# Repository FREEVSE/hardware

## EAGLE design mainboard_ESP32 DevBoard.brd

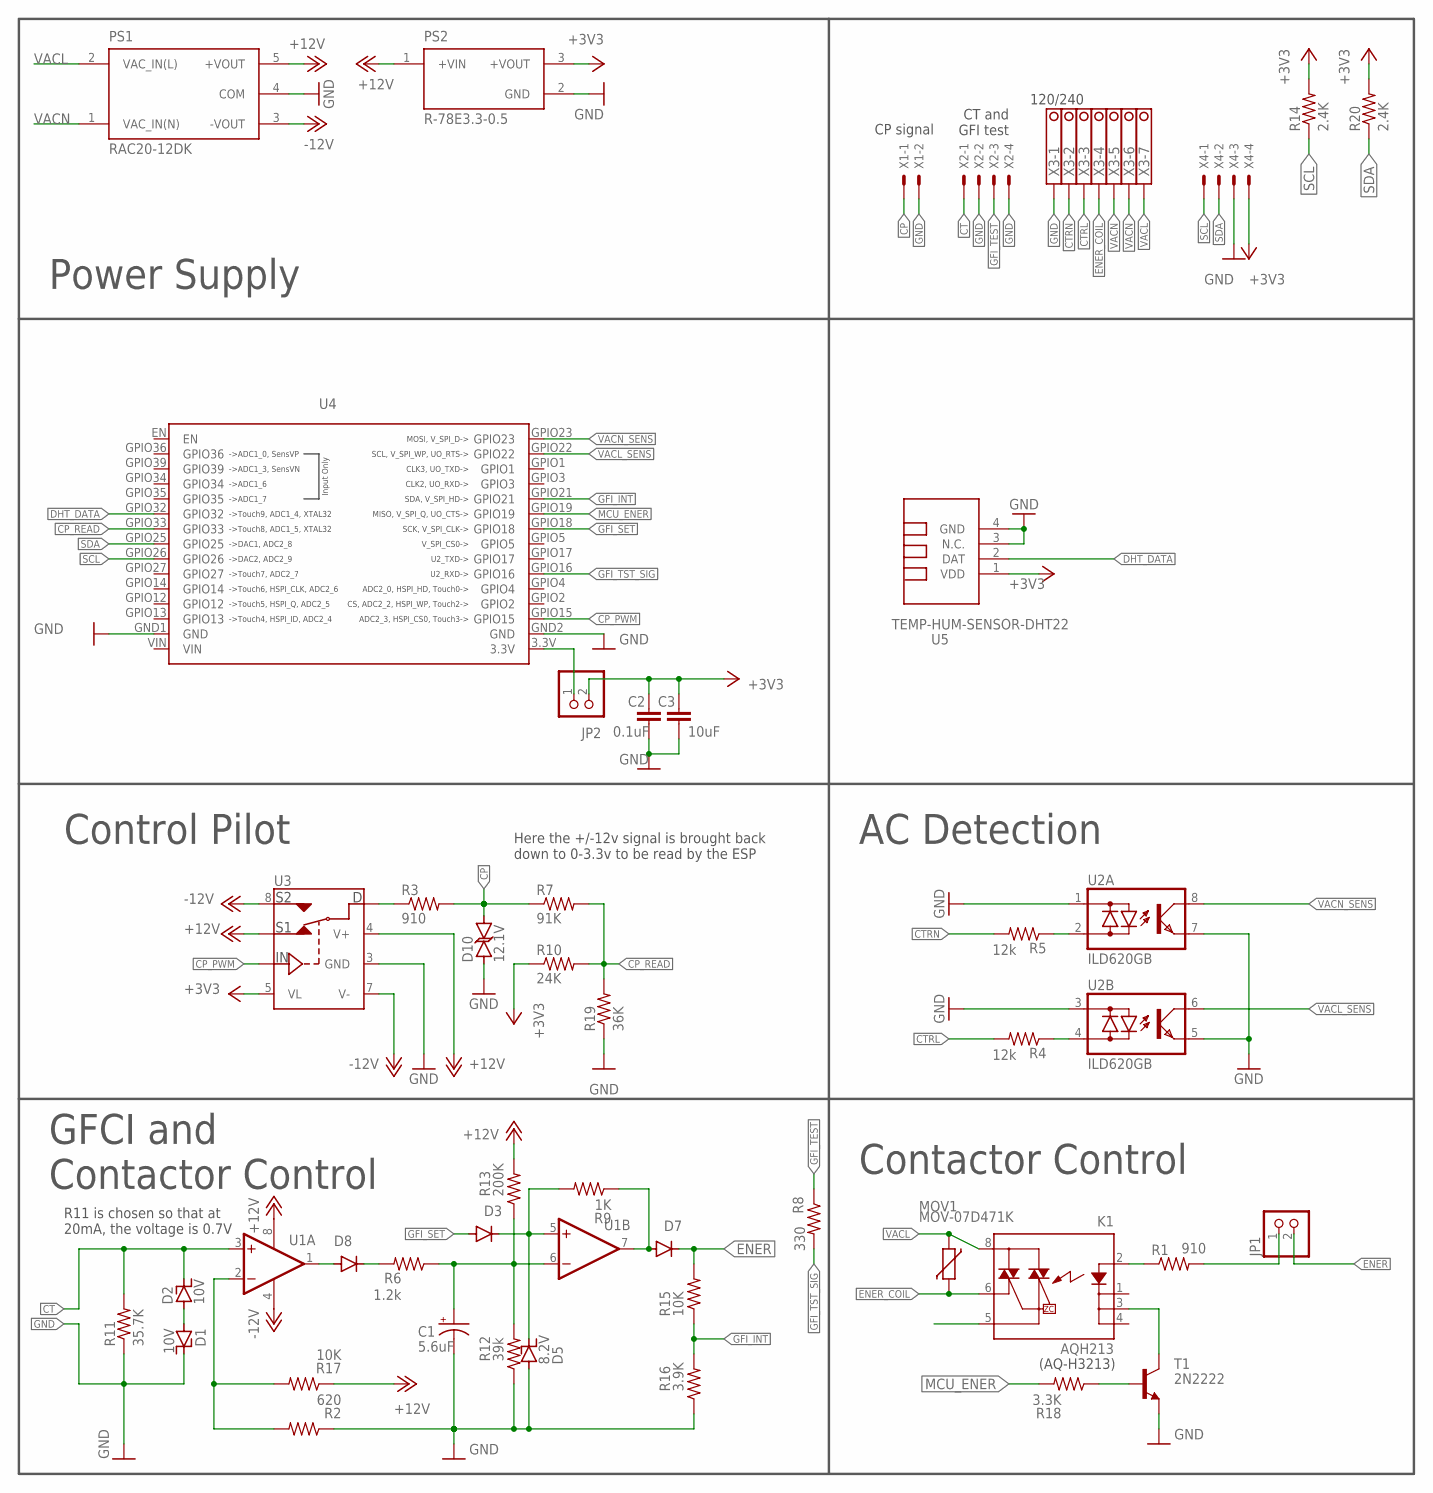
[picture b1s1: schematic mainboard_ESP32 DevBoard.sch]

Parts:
C1: 5.6uF; E2-5
C2: 0.1uF; C025-025X050
C3: 10uF; C025-050X050
D1, D2: 10V; DO35-7
D3, D7, D8: 1N4148DO35-7; DO35-7
D5: 8.2V; DO35-7
D10: 12.1V; DO15
JP1: PINHD-1X2; 1X02
JP2: PINHD-1X2/90; 1X02/90
K1: AQH213; DIL07
MOV1: MOV-07D471K; DISC-7
PS1: RAC20-12DK; CONV_RAC20-12DK
PS2: R-78E3.3-0.5; CONV_R-78E3.3-0.5
R1, R3: 910; 0204/7-L
R2: 620; 0204/7-L
R4, R5: 12k; 0204/7-L
R6: 1.2k; 0204/7-L
R7: 91K; 0204/7-L
R8: 330; 0204/7-L
R9: 1K; 0204/7-L
R10: 24K; 0204/7-L
R11: 35.7K; 0204/7-L
R12: 39k; 0204/7-L
R13: 200K; 0204/7-L
R14, R20: 2.4K; 0204/7-L
R15, R17: 10K; 0204/7-L
R16: 3.9K; 0204/7-L
R18: 3.3K; 0204/7-L
R19: 36K; 0204/7-L
T1: 2N2222; TO92-EBC
U1: LM833N; DIL08-LONG
U2: ILD620GB; DIL8
U3: DG419DJ-L; DIL08-LONG
U4: ESP32-DOIT-V1
U5: TEMP-HUM-SENSOR-DHT22
X1: JST-XH-02-PIN-LONG-PAD; JST-XH-02-PACKAGE-LONG-PAD
X2, X4: JST-XH-04-PIN-LONG-PAD; JST-XH-04-PACKAGE-LONG-PAD
X3: 1751293

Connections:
+3V3: C2.1, C3.1, JP2.2, PS2.3 (+VOUT), R10.1, R14.2, R20.2, U3.5 (VL), U5.1 (VDD), X4.4
+12V: PS1.5 (+VOUT), PS2.1 (+VIN), R13.2, R17.1, U1.8 (V+), U3.2 (S1), U3.4 (V+)
-12V: PS1.3 (-VOUT), U1.4 (V-), U3.7 (V-), U3.8 (S2)
CP: D10.C, R3.2, R7.1, X1.1
CP_PWM: U3.6 (IN), U4.GPIO15
CP_READ: R7.2, R10.2, R19.2, U4.GPIO33
CT: D2.C, R11.2, U1.3 (+IN), X2.1
CTRL: R4.2, X3.3
CTRN: R5.2, X3.2
DHT_DATA: U4.GPIO32, U5.2 (DAT)
ENER: D7.C, JP1.2, R15.2
ENER_COIL: K1.6 (DS3), MOV1.P$2 (2), X3.4
GFI_INT: R15.1, R16.2, U4.GPIO21
GFI_SET: D3.A, U4.GPIO18
GFI_TEST: R8.1, X2.3
GFI_TST_SIG: R8.2, U4.GPIO16
GND: C1.-, C2.2, C3.2, D1.C, D5.A, D10.A, PS1.4 (COM), PS2.2 (GND), R2.1, R11.1, R12.1, R16.1, R19.1, T1.E, U2.1 (AC1), U2.3 (AC1), U2.5 (E), U2.7 (E), U3.3 (GND), U4.GND1 (GND), U4.GND2 (GND), U5.3 (N.C.), U5.4 (GND), X1.2, X2.2, X2.4, X3.1, X4.3
MCU_ENER: R18.2, U4.GPIO19
unnamed: K1.2 (A), R1.1
unnamed: R2.2, R17.2, U1.2 (-IN)
unnamed: JP1.1, R1.2
unnamed: D7.A, R9.1, U1.7 (OUT)
unnamed: D1.A, D2.A
unnamed: D8.C, R6.2
unnamed: R3.1, U3.1 (D)
unnamed: C1.+, R6.1, R12.2, R13.1, U1.6 (-IN)
unnamed: JP2.1, U4.3.3V
unnamed: R18.1, T1.B
unnamed: D3.C, D5.C, R9.2, U1.5 (+IN)
unnamed: K1.3 (K1), T1.C
unnamed: D8.A, U1.1 (OUT)
unnamed: R5.1, U2.2 (AC2)
unnamed: R4.1, U2.4 (AC2)
SCL: R14.1, U4.GPIO26, X4.1
SDA: R20.1, U4.GPIO25, X4.2
VACL: K1.8 (DS1), MOV1.P$1 (1), PS1.2 (VAC_IN(L)), X3.7
VACL_SENS: U2.6 (C), U4.GPIO22
VACN: PS1.1 (VAC_IN(N)), X3.5, X3.6
VACN_SENS: U2.8 (C), U4.GPIO23
VIN: U4.VIN

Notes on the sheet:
Here the +/-12v signal is brought back down to 0-3.3v to be read by the ESP
Control Pilot
(AQ-H3213)
GFCI and Contactor Control
CP signal
CT and GFI test
120/240
Power Supply
R11 is chosen so that at 20mA, the voltage is 0.7V
AC Detection
Contactor Control

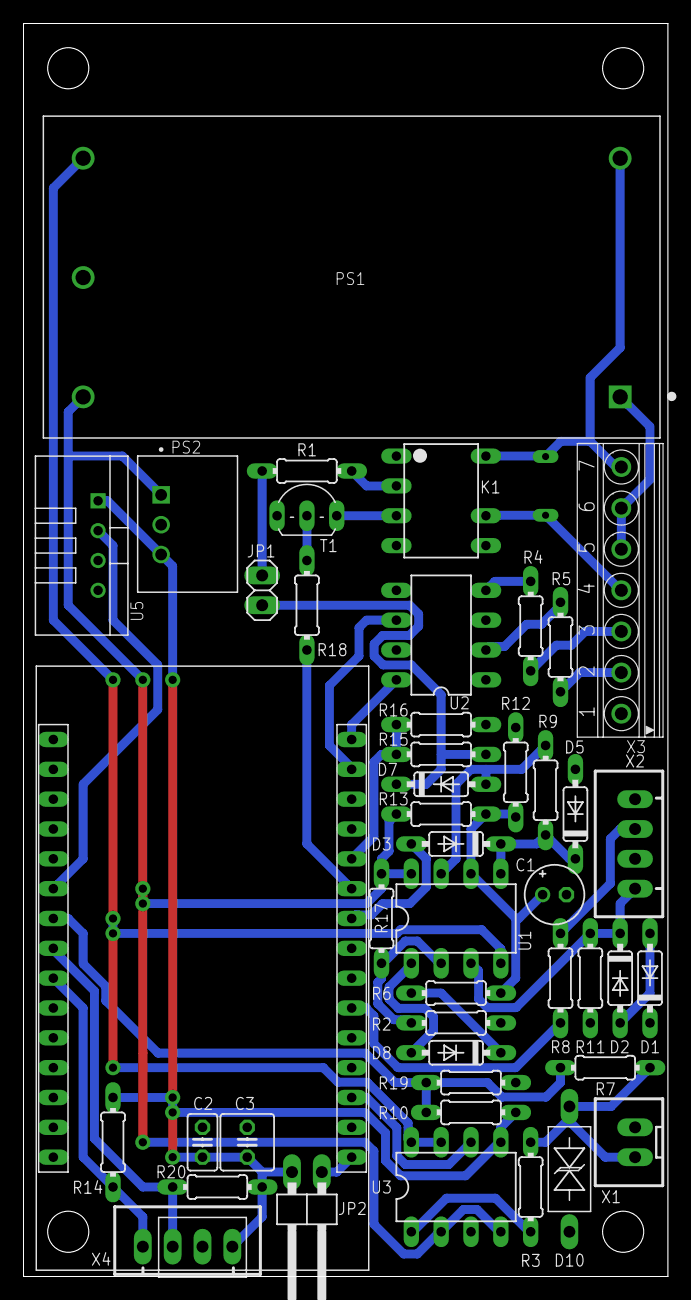
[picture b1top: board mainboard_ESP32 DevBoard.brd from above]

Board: 2 copper layers, 54.9 x 106.7 mm, 46 parts (0 on the bottom side), 39 nets.

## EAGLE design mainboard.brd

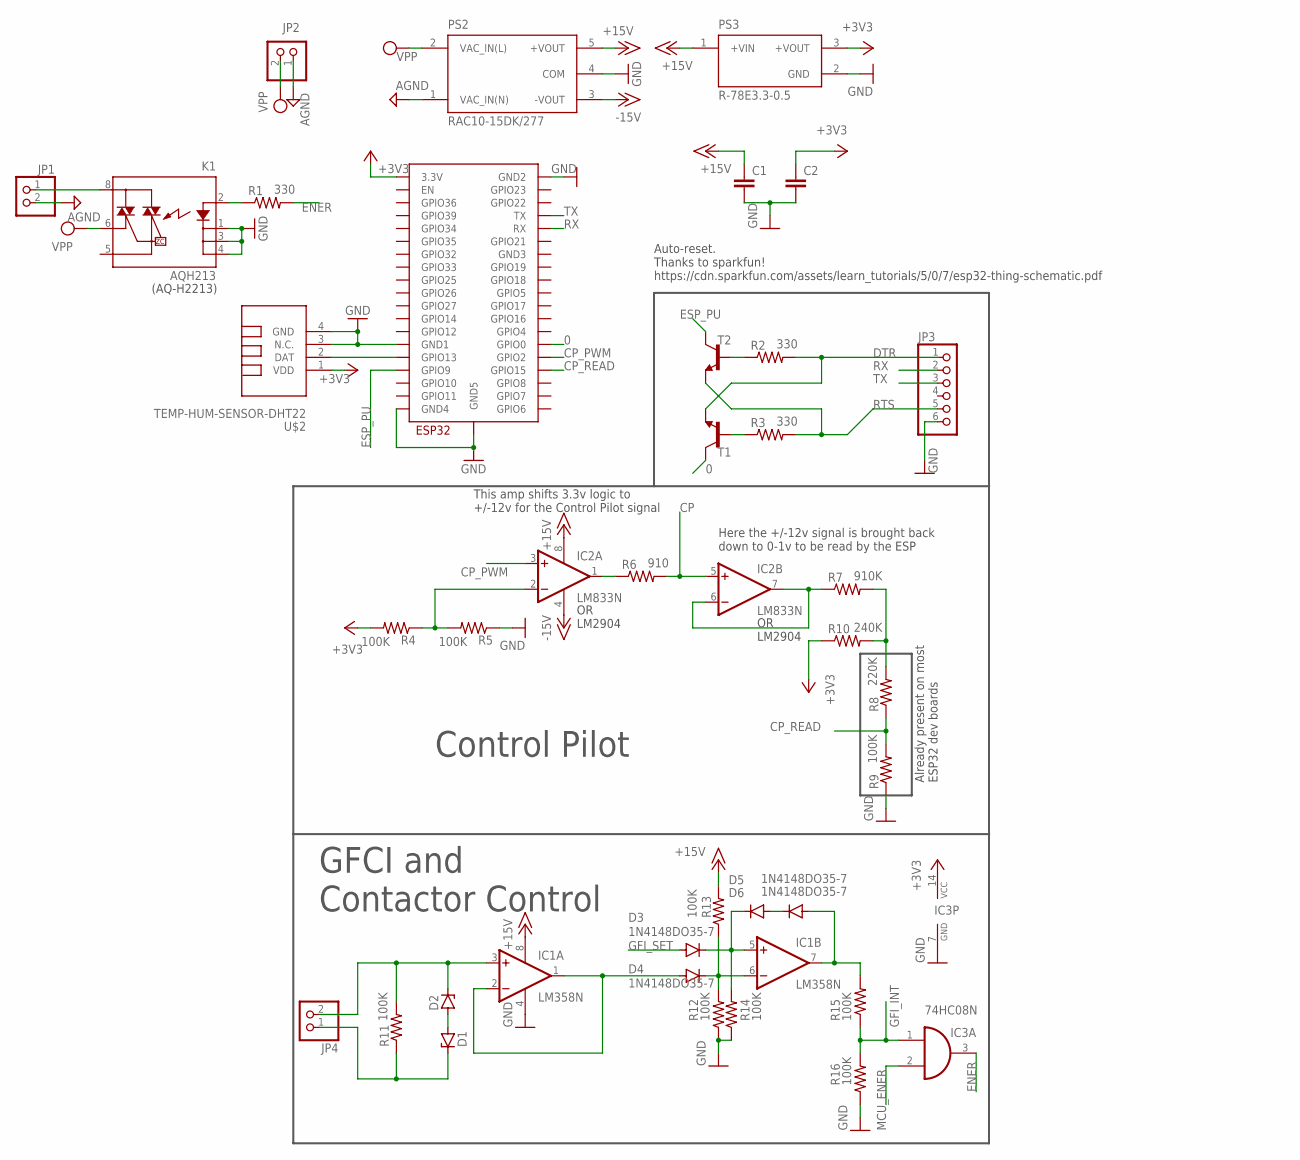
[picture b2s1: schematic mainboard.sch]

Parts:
C1, C2: C-EU025-025X050; C025-025X050
D1, D2: ZENER-DIODEDO34-7; DO34Z7
D3, D4, D5, D6: 1N4148DO35-7; DO35-7
IC1: LM358N; DIL08
IC2: LM833N; DIL08
IC3: 74HC08N; DIL14
JP1, JP2, JP4: PINHD-1X2; 1X02
JP3: PINHD-1X6; 1X06
K1: AQH213; DIL07
PS2: RAC10-15DK/277; CONV_RAC10-15DK/277
PS3: R-78E3.3-0.5; CONV_R-78E3.3-0.5
R1, R2, R3: 330; 0204/7
R4, R5, R9, R11, R12, R13, R14, R15, R16: 100K; 0204/7
R6: 910; 0204/7
R7: 910K; 0204/7
R8: 220K; 0204/7
R10: 240K; 0204/7
T1, T2: MMBT3904LT1-NPN-SOT23-BEC; SOT23-BEC
U$1: ESP32-WROOM
U$2: TEMP-HUM-SENSOR-DHT22

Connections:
0: T1.C, U$1.IO0 (GPIO0)
+3V3: C2.1, IC3.14 (VCC), PS3.3 (+VOUT), R4.2, R10.1, U$1.3V3 (3.3V), U$2.1 (VDD)
+15V: C1.1, IC1.8 (V+), IC2.8 (V+), PS2.5 (+VOUT), PS3.1 (+VIN), R13.2
-15V: IC2.4 (V-), PS2.3 (-VOUT)
AGND: JP1.2, JP2.1, PS2.1 (VAC_IN(N))
CP: IC2.5 (+IN), R6.2
CP_PWM: IC2.3 (+IN), U$1.IO2 (GPIO2)
CP_READ: R8.1, R9.2, U$1.IO15 (GPIO15)
DTR: JP3.1, R2.2, T1.E
ENER: IC3.3 (O), R1.2
ESP_PU: T2.C, U$1.SD2 (GPIO9)
GFI_INT: IC3.1 (I0), R15.1, R16.2
GFI_SET: D3.A
GND: C1.2, C2.2, IC1.4 (V-), IC3.7 (GND), JP3.6, K1.1 (K), K1.3 (K1), K1.4 (K2), PS2.4 (COM), PS3.2 (GND), R5.1, R9.1, R12.1, R14.1, R16.1, U$1.GND1, U$1.GND2, U$1.GND4, U$1.GND5, U$2.3 (N.C.), U$2.4 (GND)
MCU_ENER: IC3.2 (I1)
unnamed: K1.2 (A), R1.1
unnamed: JP1.1, K1.8 (DS1)
unnamed: U$1.IO13 (GPIO13), U$2.2 (DAT)
unnamed: D1.A, D2.A
unnamed: D2.C, IC1.3 (+IN), JP4.2, R11.2
unnamed: R2.1, T2.B
unnamed: R3.1, T1.B
unnamed: D4.A, IC1.1 (OUT), IC1.2 (-IN)
unnamed: D1.C, JP4.1, R11.1
unnamed: D6.A, IC1.7 (OUT), R15.2
unnamed: D5.A, D6.C
unnamed: D3.C, D5.C, IC1.5 (+IN), R14.2
unnamed: D4.C, IC1.6 (-IN), R12.2, R13.1
unnamed: IC2.2 (-IN), R4.1, R5.2
unnamed: IC2.1 (OUT), R6.1
unnamed: IC2.6 (-IN), IC2.7 (OUT), R7.1
unnamed: R7.2, R8.2, R10.2
RTS: JP3.5, R3.2, T2.E
RX: JP3.2, U$1.RX
TX: JP3.3, U$1.TX
VPP: JP2.2, K1.6 (DS3), PS2.2 (VAC_IN(L))

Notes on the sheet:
Already present on most ESP32 dev boards
This amp shifts 3.3v logic to +/-12v for the Control Pilot signal
Here the +/-12v signal is brought back down to 0-1v to be read by the ESP
OR LM2904
Auto-reset. Thanks to sparkfun! https://cdn.sparkfun.com/assets/learn_tutorials/5/0/7/esp32-thing-schematic.pdf
Control Pilot
(AQ-H2213)
GFCI and Contactor Control

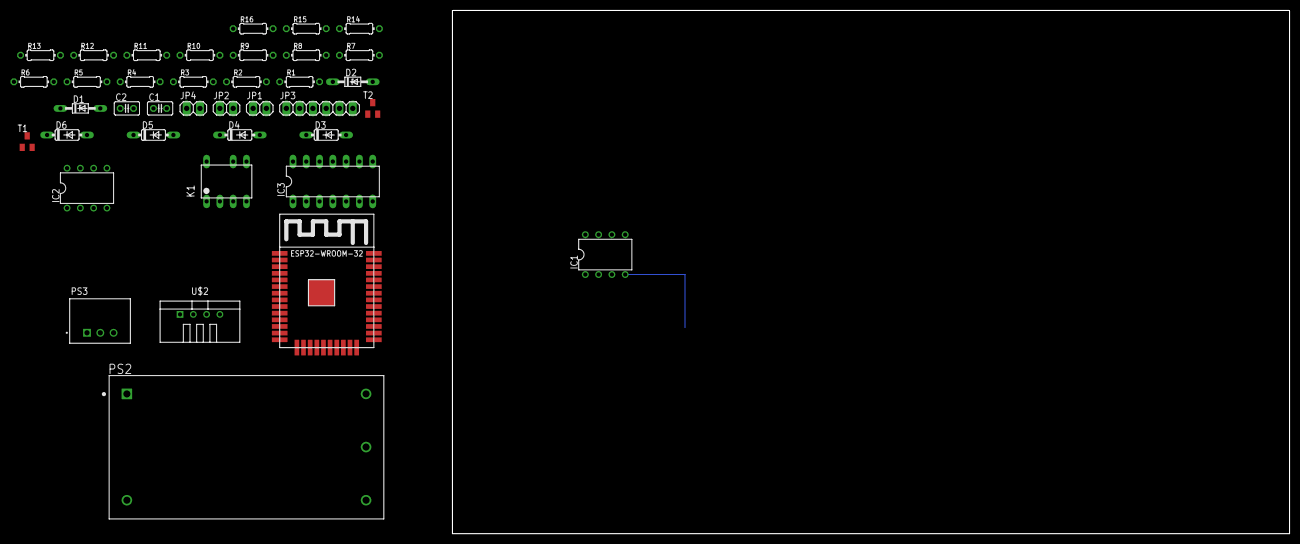
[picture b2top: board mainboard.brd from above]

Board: 2 copper layers, 160.0 x 100.0 mm, 38 parts (0 on the bottom side), 34 nets.

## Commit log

2019-12-28 Completed routing first try of board. Some pin changes to fit the board better. Added puldown and jumper to prevent accidental coil energize.
2019-12-29 Tweaked resistor on GFI circuit to allow 3.3v logic to set the latch
2019-12-29 Added header to disconnect 3.3v output from esp to 3.3 rail. Added LED to indicate when contactor is energized. Added I2C connector. Added mounting holes.
2019-12-31 Made all traces as big as possible. Pads also. Added some layers for CAM outputs. Added cam job file
2020-01-10 Updated ignore file. Made some adjustments after making the first board.
2020-01-13 Made board single-sided friendly (P2P wiring needed). Tweaked some more resistor values. Added missing resistor to CP read level shifter
2020-01-13 Corrected some via sizes
2020-01-16 Switched to +-12v, tweaked some R values to fit new psu. Also swapped CP opamp for an r2r one
2020-02-11 Added DG419 in place of op amp.
2020-04-30 Added optos for sensing L and N (l1/l2)
2020-05-11 Moved resistor on line sense for a tight, but good fit. cam outputs used for board 2
2020-05-13 Added missing mains class
2020-05-17 Added header for ac detection after contactor. Cleaned up schematic.
2020-05-19 Swapped ac headers for one big one and added dedicated earth terminal
2020-06-25 Adjusted labels for PCB manufacture
2020-07-01 Cleaned labels
2020-07-11 Reworked GFCI to account for noise on the line. Swapped out AND gate for 2 mosfets. Removed mostly useless caps from PSU outputs, caps should be closer to devices
2020-07-17 Re-worked GFCI to be tolerant of transient spikes. Removed some components because of it
2020-07-26 Completed new GFCI circuit
2020-07-31 Corrected some component values that were wrong during assembly
2020-07-31 Added start of theory of operation document
2020-08-02 Creating the BOM on digikey uncovered some footprint mismatches. They havee been corrected
2020-08-04 Added pullup resistors for I2C bus
2020-08-13 Minor adjustments
2020-08-14 Added project specific library
2020-11-07 Not sure what I changed, but I trust myself...
2021-01-30 Changed TVS diode to bi-directional P/N. Enlarged holes because fit was too tight.
2021-04-29 Create LICENSE

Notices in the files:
parts and their libraries:
diy-modules: Released under the Creative Commons Attribution 4.0 International License: http://creativecommons.org/licenses/by/4.0
